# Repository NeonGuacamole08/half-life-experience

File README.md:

## I made a Toadie! A Toad-shaped Starbie!

I first downloaded the care package provided by Half-Life! 
Then I watched No. 3: Installing symbol libraries, footprints, and 3D step files in Kicad 9video by Electronicx on YouTube to figure out how to download the schematics and footprints file from the guide. I had absolutely no idea before I started this endeavor about how one makes a circuit, so this was a totally new world to me, and the guide was very useful. 

## The Schematics

So, following the guide, I uploaded the files AND got it working. 
### To upload components, click the letter A
This will allow you to choose components like sensors or boards. For this specific one, we used a XIAO-ESP32-C3

### To upload power symbols like gnds and volts batter, click the letter P

This will allow you to make connections.
### To name or rather specify how certain parts will be soldered or connected, click the letter L

Since Starbie is a handheld digital pet, we need more than just the motherboard. 
### Components
<li>2 Buttons </li>  
<li>a DHT11 Environmental Sensor </li> 
<li>an OLED </li>
<li>and an MPU5060</li>

Wire them like this

### Assign Footprints 

It should lead you to a pop-up like so; match the sensors like

##  THE PCB
Once all the components are connected, we can start assigning footprints to the symbols we have here. Footprints are what get physically drawn on the PCB. To do this, click the "run footprint assignment tool" in the top right.

To make the PCB, you can actually just convert your schematic into the alignment parts by clicking on the 
This allows you to work directly on your PCB! Then you need to come up with the shape of your board. I wanted mine to look like Toad, but I suck at drawing, so I used the reference image options:

Then, using the edge cuts on layers, you can use the Draw Polygons tool to draw the approximate shape of your board.

Then you need to route your PCB so that all the connections are linked. To do that select the F.cu  layer

Then click on any blue lines to fill them. You can also click on F for  the connections to be filled

### DRC (or Design Rules Check) is a tool that automatically checks for PCB design mistakes, such as disconnected traces or other various errors.

You can access it via the button on the top right:

Then click on Run DRC to run the analysis 

To have access to the 3d render, click on this:

## DONE DONE DONEE

## Bill of Materials (BOM)

| Item | Qty | Supplier | Cost/item | Total Cost | Link |
| :--- | :---: | :--- | ---: | ---: | :--- |
| **AS7262 Visible Spectrometer Breakout**<br><sub>Reads 6 visible channels (450nm–650nm) via I2C (A4/A5). Detects early chlorosis/leaf stress.</sub> | 1 | Adafruit | $24.95 | $24.95 | [Link](https://www.adafruit.com/product/3779) |
| **Capacitive Soil Moisture Sensor v1.2**<br><sub>Measures water content</sub> | 1 | DFRobot | $3.00 | $3.00 | [Link](https://www.dfrobot.com/product-1385.html) |
| **MAX485 TTL to RS485 Transceiver Module**<br><sub>Converts RS485 Modbus signal from industrial soil probes into serial data Arduino can read</sub> | 1 | DFRobot | $2.50 | $2.50 | [Link](https://www.dfrobot.com/product-1024.html) |
| **Estimated total shipping** | 1 | — | — | $0 | — |
| **Total** | | | | **$30.45** | |

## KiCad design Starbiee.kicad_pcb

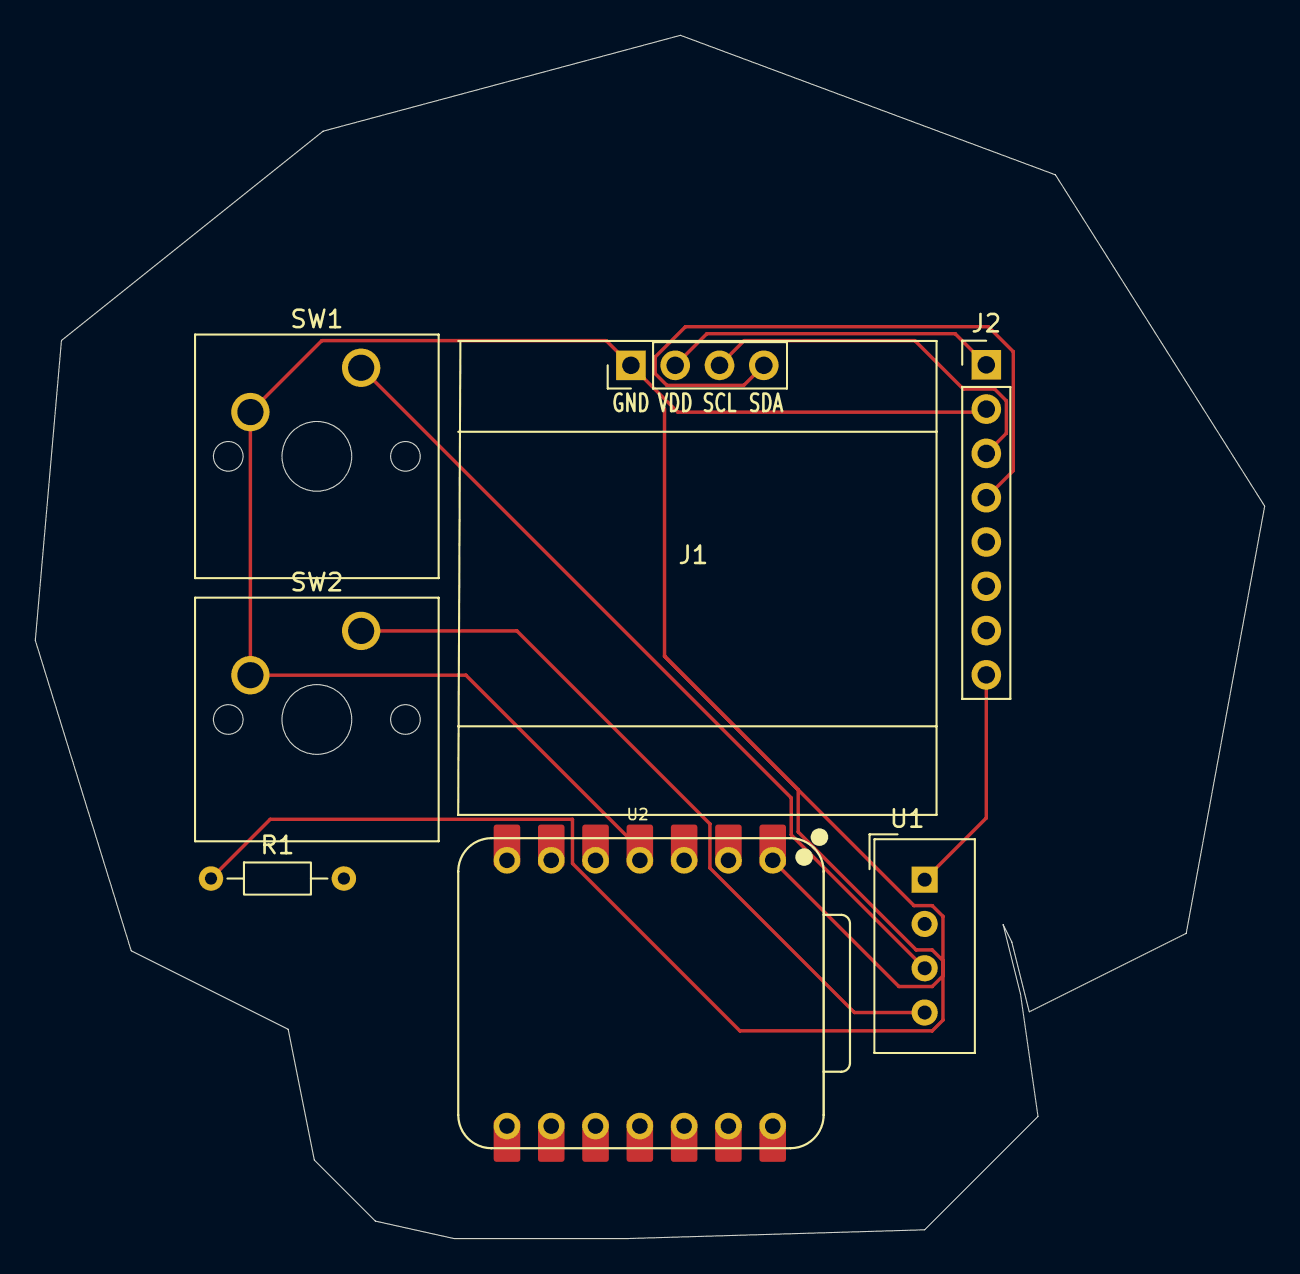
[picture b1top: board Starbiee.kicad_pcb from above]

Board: 2 copper layers, 70.5 x 69.0 mm, 7 parts (0 on the bottom side), 8 nets.

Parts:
J1: Conn_01x04_Pin; Display_128x64_096_I2C
J2: Conn_01x08_Pin; PinHeader_1x08_P2.54mm_Vertical
R1: 10k; R_Axial_DIN0204_L3.6mm_D1.6mm_P7.62mm_Horizontal
SW1, SW2: SW_Push; SW_Cherry_MX_1.00u_PCB
U1: XIAO-ESP32-C3-SMD; Aosong_DHT11_5.5x12.0_P2.54mm
U2: DHT11; XIAO-ESP32-C6-DIP

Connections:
+3.3V: J1.2, J2.1, R1.1, U2.1 (VDD)
/DHT11 DATA: R1.2, U1.2 (D1), U2.2 (DATA)
/GPIO2: SW1.1, U1.3 (D2)
/GPIO3: SW2.1, U1.4 (D3)
/SCL: J1.3, J2.3
/SDA: J1.4, J2.4
/x: J2.5, J2.6, J2.7, J2.8, U1.1 (D0)
GND: J1.1, J2.2, SW1.2, SW2.2, U2.4 (GND)
